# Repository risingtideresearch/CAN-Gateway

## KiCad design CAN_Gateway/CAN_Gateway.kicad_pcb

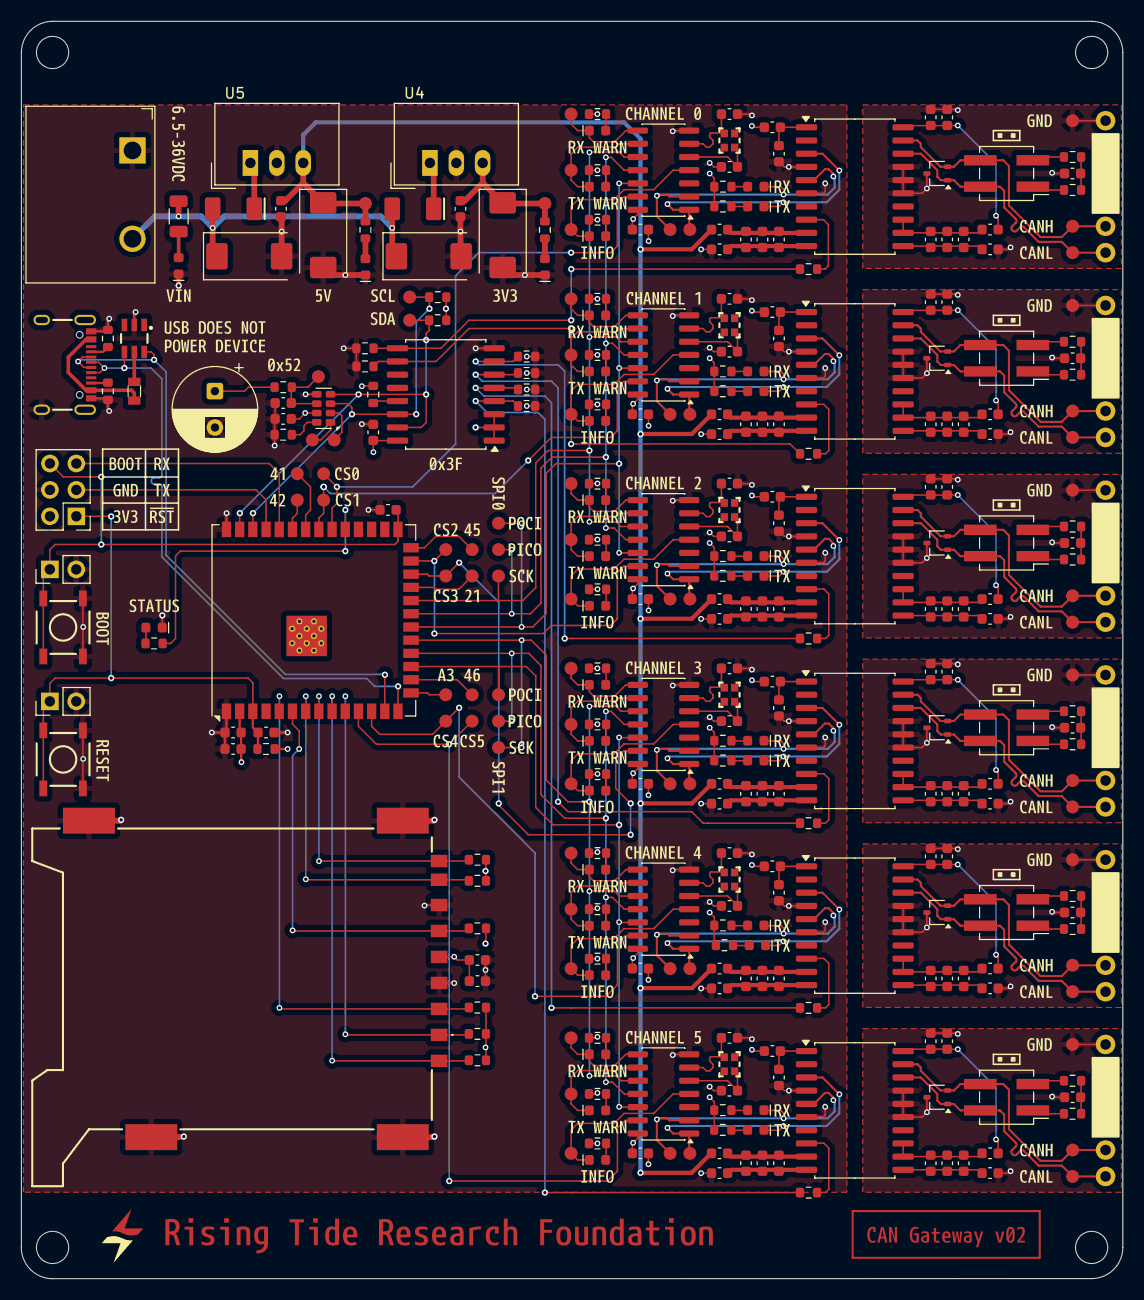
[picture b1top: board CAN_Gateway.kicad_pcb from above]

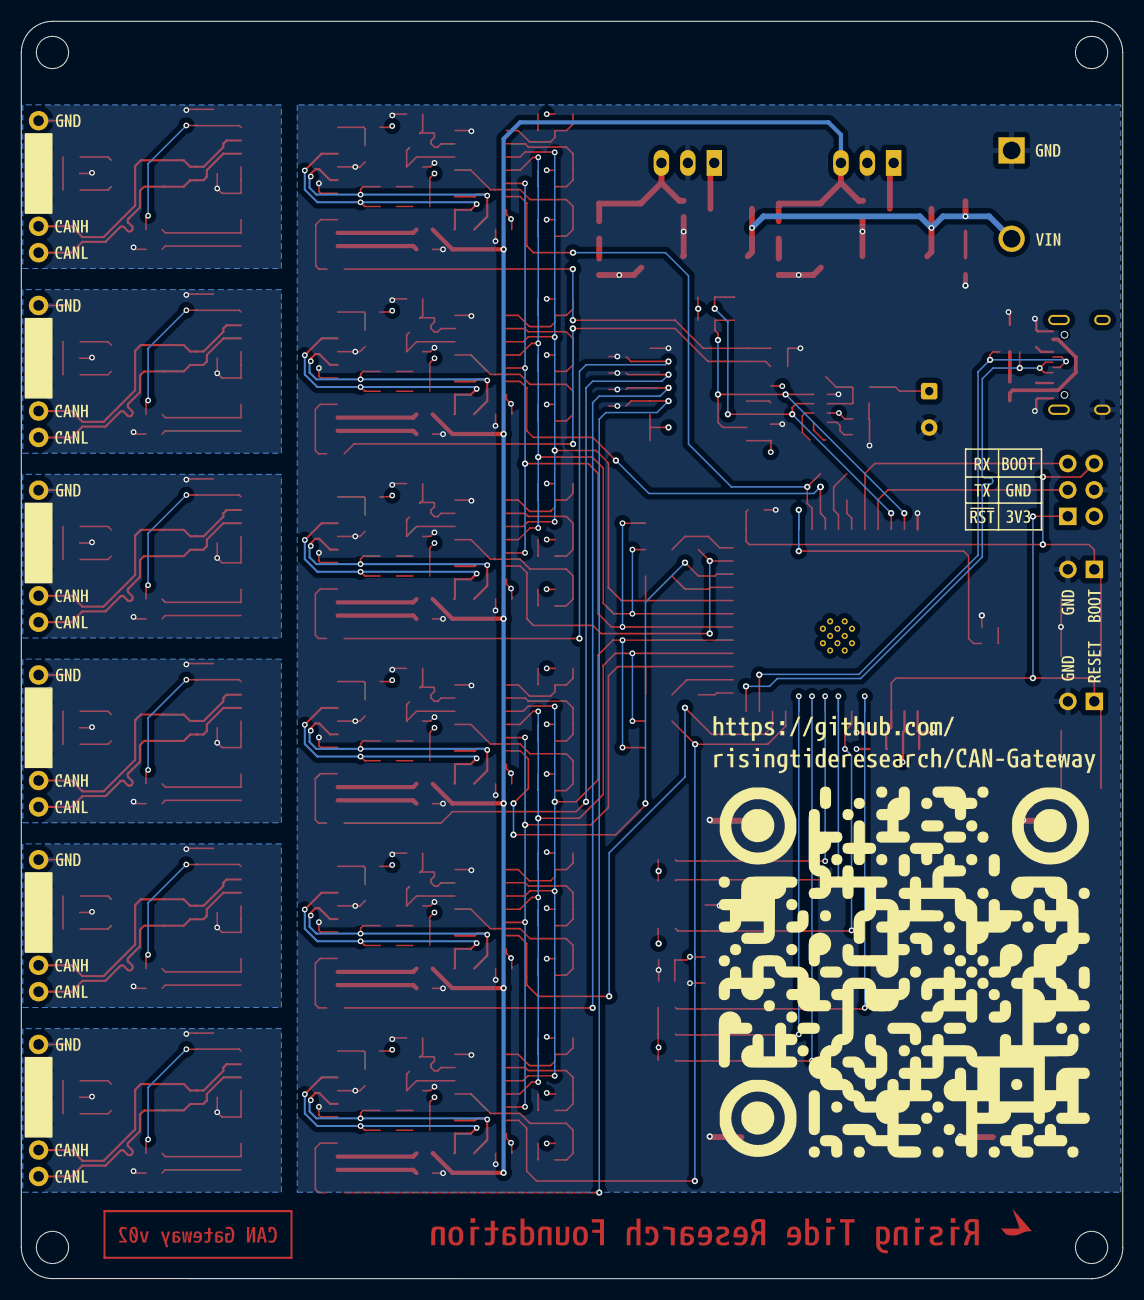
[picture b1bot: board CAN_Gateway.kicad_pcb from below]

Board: 4 copper layers, 106.0 x 121.0 mm, 481 parts (31 on the bottom side), 209 nets.

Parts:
C1, C3, C7, C16, C20, C21, C23, C27, C30, C37, C39, C43, C52, C54, C56, C60, C67, C69, C73, C83, C85, C89, C90: 0.1uF; C_0603_1608Metric
C2, C6, C12, C17, C22, C26, C33, C38, C42, C46, C55, C59, C63, C68, C72, C77, C81, C84, C88, C93: 10uF; C_0603_1608Metric
C4, C14, C24, C35, C40, C48, C50, C51, C57, C65, C70, C79, C86, C95: 10nF; C_0603_1608Metric
C5, C13, C25, C34, C41, C47, C58, C64, C71, C74, C78, C87, C94: 1.0uF; C_0603_1608Metric
C10, C31, C44, C61, C75, C91: 4.7nF; C_0603_1608Metric
C11, C15, C32, C36, C45, C49, C62, C66, C76, C80, C92, C96: 15pF; C_0603_1608Metric
C18, C19, C28, C29: 10uF; CP_EIA-7343-30_AVX-N
C53: 1F; CP_Radial_D8.0mm_P3.50mm
C82: 4.7uF; C_0603_1608Metric
D1, D2, D3, D10, D11, D12, D17, D18, D19, D23, D24, D25, D29, D30, D31, D36, D37, D38, D42, D43, D44: Red; LED_0603_1608Metric
D4, D5, D13, D14, D20, D21, D26, D27, D32, D33, D39, D40: Green; LED_0603_1608Metric
D7, D16, D22, D28, D34, D41: ESD2CANxx24-Q1; SOT-323_SC-70
D8, D15: SK34A; SMA
D9: DT1042-04SO; SOT23-6
D35: Blue; LED_0603_1608Metric
F1: 6V/0.5A/1A; 0805
J1, J6, J8, J10, J12, J19: Conn 01x06 Socket; 1x06
J2: Screw Terminal 2Pos 8.5mm Pitch; TerminalBlock_DoraboDBT10_8.5mm
J3, J7, J9, J11, J15, J18: Conn_02x02_Pin; PinHeader_2x02_P2.54mm_Vertical_SMD
J4: USB-C Receptacle; USB-C_16
J5: SDCard Push-Lock FPS009-4200-0; SDCard_PushLock_FPS00942000
J13: Conn 02x03 Odd Even; PinHeader_2x03_P2.54mm_Vertical
J14, J17: Conn 01x02 Pin; PinHeader_1x02_P2.54mm_Vertical
L1, L2, L3, L4, L5, L6, L7, L8, L9, L10, L11, L12, L13, L14, L15, L16, L17, L18, L19, L20, L21, L22, L23, L24, L25, L26, L27, L28, L29, L30: 330 OHM; C_0603_1608Metric
R1, R2, R3, R16, R17, R18, R23, R24, R25, R33, R34, R35, R40, R41, R42, R51, R52, R53: 330; R_0603_1608Metric
R4, R5, R19, R20, R26, R27, R36, R37, R43, R44, R54, R55: 68; R_0603_1608Metric
R6, R7, R21, R22, R28, R29, R38, R39, R48, R49, R59, R60: 60.4R; R_0603_1608Metric
R8, R9, R10, R11, R12, R13, R31, R32, R45, R61, R62, R63, R64, R65, R66: 10k; R_0603_1608Metric
R14, R15: 5.1k; R_0603_1608Metric
R30, R57: 1k; R_0603_1608Metric
R46, R47: 2.2k; R_0603_1608Metric
R50, R58: 470; R_0603_1608Metric
R56: 2.0k; R_1206_3216Metric
R67, R68, R69, R70, R71, R72: 4.7k; R_0603_1608Metric
SW1, SW2: SMD_5.2x5.2mm_h1.9mm; Push_SMD_5.2x5.2mm_h1.9mm
TP1, TP2, TP3, TP4, TP5, TP6, TP7, TP8, TP9, TP10, TP11, TP12, TP13, TP14, TP15, TP16, TP17, TP18, TP19, TP20, TP21, TP22, TP23, TP24, TP25, TP26, TP27, TP28, TP29, TP30, TP31, TP32, TP33, TP34, TP35, TP36, TP37, TP38, TP39, TP40, TP41, TP42, TP43, TP44, TP45, TP46, TP47, TP48, TP49, TP50, TP51, TP52, TP53, TP54, TP55, TP56, TP57, TP58, TP59, TP60, TP61, TP62, TP63, TP64, TP65, TP66, TP67, TP68, TP69, TP70, TP71, TP72, TP73: 1.25mm; TestPoint-1.25mm
U2, U6, U8, U12, U14, U17: ISOW1044; SOIC-20W_7.5x12.8mm_P1.27mm
U3, U7, U9, U13, U15, U18: MCP2518FD; SOIC-14_3.9x8.7mm_P1.27mm
U4: DCDC TSR1-2433E 3.3V; Converter_DCDC_TRACO_TSR-1_THT
U5: DCDC TSR1-2450E 5V; Converter_DCDC_TRACO_TSR-1_THT
U10: RV-3028-C7; MicroCrystal_C7_SON-8_1.5x3.2mm_P0.9mm
U11: TCA9534; SOIC-16W_7.5x10.3mm_P1.27mm
U16: ESP32-S3-WROOM-1U-N16R2; ESP32-S3-WROOM-1U
Y1, Y2, Y3, Y4, Y5, Y6: 20MHz; Crystal_SMD_2.0x1.6mm
kibuzzard-69A580A1: G***; kibuzzard-69A580A1
kibuzzard-69A580AE: G***; kibuzzard-69A580AE
kibuzzard-69A580BE: G***; kibuzzard-69A580BE
kibuzzard-69A580C7: G***; kibuzzard-69A580C7
kibuzzard-69A580D6: G***; kibuzzard-69A580D6
kibuzzard-69A580DE: G***; kibuzzard-69A580DE
kibuzzard-69A58259: G***; kibuzzard-69A58259
kibuzzard-699FC53E: G***; kibuzzard-699FC53E
kibuzzard-699FC70E, kibuzzard-699FC70E#2, kibuzzard-699FC70E#3, kibuzzard-699FC70E#4, kibuzzard-699FC70E#5, kibuzzard-699FC70E#6, kibuzzard-699FC70E#7, kibuzzard-699FC70E#8, kibuzzard-699FC70E#9, kibuzzard-699FC70E#10, kibuzzard-699FC70E#11, kibuzzard-699FC70E#12: G***; kibuzzard-699FC70E
kibuzzard-699FC89D, kibuzzard-699FC89D#2, kibuzzard-699FC89D#3, kibuzzard-699FC89D#4, kibuzzard-699FC89D#5, kibuzzard-699FC89D#6: G***; kibuzzard-699FC89D
kibuzzard-699FC682: G***; kibuzzard-699FC682
kibuzzard-699FC727, kibuzzard-699FC727#2, kibuzzard-699FC727#3, kibuzzard-699FC727#4, kibuzzard-699FC727#5, kibuzzard-699FC727#6, kibuzzard-699FC727#7, kibuzzard-699FC727#8, kibuzzard-699FC727#9, kibuzzard-699FC727#10, kibuzzard-699FC727#11, kibuzzard-699FC727#12: G***; kibuzzard-699FC727
kibuzzard-699FC895, kibuzzard-699FC895#2, kibuzzard-699FC895#3, kibuzzard-699FC895#4, kibuzzard-699FC895#5, kibuzzard-699FC895#6: G***; kibuzzard-699FC895
kibuzzard-699FCC6A, kibuzzard-699FCC6A#2, kibuzzard-699FCC6A#3, kibuzzard-699FCC6A#4, kibuzzard-699FCC6A#5, kibuzzard-699FCC6A#6: G***; kibuzzard-699FCC6A
kibuzzard-699FCC73, kibuzzard-699FCC73#2, kibuzzard-699FCC73#3, kibuzzard-699FCC73#4, kibuzzard-699FCC73#5, kibuzzard-699FCC73#6: G***; kibuzzard-699FCC73
kibuzzard-699FCC79, kibuzzard-699FCC79#2, kibuzzard-699FCC79#3, kibuzzard-699FCC79#4, kibuzzard-699FCC79#5, kibuzzard-699FCC79#6: G***; kibuzzard-699FCC79
kibuzzard-699FD0A7: G***; kibuzzard-699FD0A7
kibuzzard-699FD0AC: G***; kibuzzard-699FD0AC
kibuzzard-699FD0B2: G***; kibuzzard-699FD0B2
kibuzzard-699FD0B9: G***; kibuzzard-699FD0B9
kibuzzard-699FD0BF: G***; kibuzzard-699FD0BF
kibuzzard-699FD1A2: G***; kibuzzard-699FD1A2
kibuzzard-699FD1B1, kibuzzard-699FD1B1#2: G***; kibuzzard-699FD1B1
kibuzzard-699FD1CD: G***; kibuzzard-699FD1CD
kibuzzard-699FD1DB: G***; kibuzzard-699FD1DB
kibuzzard-699FD2FA, kibuzzard-699FD2FA#2: G***; kibuzzard-699FD2FA
kibuzzard-699FD3EC: G***; kibuzzard-699FD3EC
kibuzzard-699FD05A: G***; kibuzzard-699FD05A
kibuzzard-699FD6AC: G***; kibuzzard-699FD6AC
kibuzzard-699FD6B7: G***; kibuzzard-699FD6B7
kibuzzard-699FD7B6: G***; kibuzzard-699FD7B6
kibuzzard-699FD010, kibuzzard-699FD010#2, kibuzzard-699FD010#3, kibuzzard-699FD010#4, kibuzzard-699FD010#5, kibuzzard-699FD010#6, kibuzzard-699FD010#7, kibuzzard-699FD010#8, kibuzzard-699FD010#9, kibuzzard-699FD010#10, kibuzzard-699FD010#11, kibuzzard-699FD010#12: G***; kibuzzard-699FD010
kibuzzard-699FD27D, kibuzzard-699FD27D#2: G***; kibuzzard-699FD27D
kibuzzard-699FD28D, kibuzzard-699FD28D#2: G***; kibuzzard-699FD28D
kibuzzard-699FD31B, kibuzzard-699FD31B#2: G***; kibuzzard-699FD31B
kibuzzard-699FD36B: G***; kibuzzard-699FD36B
kibuzzard-699FD67D: G***; kibuzzard-699FD67D
kibuzzard-699FD77B: G***; kibuzzard-699FD77B
kibuzzard-699FD269, kibuzzard-699FD269#2: G***; kibuzzard-699FD269
kibuzzard-699FD306, kibuzzard-699FD306#2, kibuzzard-699FD306#3, kibuzzard-699FD306#4, kibuzzard-699FD306#5: G***; kibuzzard-699FD306
kibuzzard-699FD386, kibuzzard-699FD386#2: G***; kibuzzard-699FD386
kibuzzard-699FD396: G***; kibuzzard-699FD396
kibuzzard-699FD567: G***; kibuzzard-699FD567
kibuzzard-699FD585: G***; kibuzzard-699FD585
kibuzzard-699FD699: G***; kibuzzard-699FD699
kibuzzard-699FD750: G***; kibuzzard-699FD750
kibuzzard-699FDA3C, kibuzzard-699FDA3C#2: G***; kibuzzard-699FDA3C
kibuzzard-699FDA5E, kibuzzard-699FDA5E#2: G***; kibuzzard-699FDA5E
kibuzzard-699FDA54, kibuzzard-699FDA54#2: G***; kibuzzard-699FDA54
kibuzzard-699FDA91: G***; kibuzzard-699FDA91
kibuzzard-699FDAA6: G***; kibuzzard-699FDAA6
kibuzzard-699FE3A4: G***; kibuzzard-699FE3A4
kibuzzard-699FE10E: G***; kibuzzard-699FE10E

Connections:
3.3V: C7.1, C16.1, C17.1, C19.1, C20.1, C27.1, C43.1, C51.1, C52.1, C60.1, C73.1, C81.1, C82.1, C89.1, J5.4 (VDD), J13.2, L1.1, L6.1, L11.1, L16.1, L21.1, L26.1, R1.2, R2.2, R3.2, R4.2, R5.2, R8.2, R9.2, R10.2, R11.2, R12.2, R13.2, R16.2, R17.2, R18.2, R19.2, R20.2, R23.2, R24.2, R25.2, R26.2, R27.2, R31.2, R33.2, R34.2, R35.2, R36.2, R37.2, R40.2, R41.2, R42.2, R43.2, R44.2, R45.2, R46.2, R47.1, R51.2, R52.2, R53.2, R54.2, R55.2, R58.2, TP9.1, U3.14 (VDD), U4.3 (Vout), U7.14 (VDD), U9.14 (VDD), U10.7 (VDD), U11.1 (A0), U11.2 (A1), U11.3 (A2), U11.16 (VDD), U13.14 (VDD), U15.14 (VDD), U16.2 (VDD), U18.14 (VDD)
5V: C29.1, C30.1, L4.1, L9.1, L14.1, L19.1, L24.1, L29.1, R57.2, TP12.1, U5.3 (Vout)
/CAN0+: D4.1 (K), TP2.1, U2.5 (RXD), U3.2 (RXCAN)
/CAN0-: D5.1 (K), TP3.1, U2.3 (TXD), U3.1 (TXCAN)
/CAN0_N: D7.1 (A1), J3.2, J19.6, TP5.1, U2.18 (CANL)
/CAN0_P: D7.2 (A2), J3.4, J19.5, TP4.1, U2.19 (CANH)
/CAN1+: D13.1 (K), TP11.1, U6.5 (RXD), U7.2 (RXCAN)
/CAN1-: D14.1 (K), TP13.1, U6.3 (TXD), U7.1 (TXCAN)
/CAN1_N: D16.1 (A1), J1.6, J7.2, TP15.1, U6.18 (CANL)
/CAN1_P: D16.2 (A2), J1.5, J7.4, TP14.1, U6.19 (CANH)
/CAN2+: D20.1 (K), TP20.1, U8.5 (RXD), U9.2 (RXCAN)
/CAN2-: D21.1 (K), TP21.1, U8.3 (TXD), U9.1 (TXCAN)
/CAN2_N: D22.1 (A1), J6.6, J9.2, TP23.1, U8.18 (CANL)
/CAN2_P: D22.2 (A2), J6.5, J9.4, TP22.1, U8.19 (CANH)
/CAN3+: D26.1 (K), TP31.1, U12.5 (RXD), U13.2 (RXCAN)
/CAN3-: D27.1 (K), TP32.1, U12.3 (TXD), U13.1 (TXCAN)
/CAN3_N: D28.1 (A1), J8.6, J11.2, TP34.1, U12.18 (CANL)
/CAN3_P: D28.2 (A2), J8.5, J11.4, TP33.1, U12.19 (CANH)
/CAN4+: D32.1 (K), TP39.1, U14.5 (RXD), U15.2 (RXCAN)
/CAN4-: D33.1 (K), TP42.1, U14.3 (TXD), U15.1 (TXCAN)
/CAN4_N: D34.1 (A1), J10.6, J15.2, TP44.1, U14.18 (CANL)
/CAN4_P: D34.2 (A2), J10.5, J15.4, TP43.1, U14.19 (CANH)
/CAN5+: D39.1 (K), TP49.1, U17.5 (RXD), U18.2 (RXCAN)
/CAN5-: D40.1 (K), TP50.1, U17.3 (TXD), U18.1 (TXCAN)
/CAN5_N: D41.1 (A1), J12.6, J18.2, TP52.1, U17.18 (CANL)
/CAN5_P: D41.2 (A2), J12.5, J18.4, TP51.1, U17.19 (CANH)
CAN0_EN: R65.2, R67.1, U11.9 (P4)
CAN1_EN: R66.2, R68.1, U11.10 (P5)
CAN2_EN: R64.2, R69.1, U11.7 (P3)
CAN3_EN: R63.2, R70.1, U11.6 (P2)
CAN4_EN: R62.2, R71.1, U11.5 (P1)
CAN5_EN: R61.2, R72.1, U11.4 (P0)
CS_CAN0: TP60.1, U3.13 (~CS), U16.32 (IO39)
CS_CAN1: TP61.1, U7.13 (~CS), U16.33 (IO40)
CS_CAN2: TP65.1, U9.13 (~CS), U16.25 (IO48)
CS_CAN3: TP64.1, U13.13 (~CS), U16.24 (IO47)
CS_CAN4: TP58.1, U15.13 (~CS), U16.12 (IOA8)
CS_CAN5: TP59.1, U16.11 (IOA18), U18.13 (~CS)
ESP32_EN: C74.1, J13.1, J14.1, R45.1, SW1.2, U16.3 (EN)
ESP32_RXD: J13.5, U16.36 (RXD0/IO44)
ESP32_TXD: J13.3, U16.37 (TXD0/IO43)
ESP_BOOT: C90.1, J13.6, J17.1, SW2.2, U16.27 (IO0)
ESP_STATUS: R50.2, U16.31 (IO38)
GND: C3.1, C7.2, C11.1, C15.1, C16.2, C17.2, C18.2, C19.2, C20.2, C23.1, C27.2, C28.2, C29.2, C30.2, C32.1, C36.1, C39.1, C43.2, C45.1, C49.1, C50.2, C51.2, C52.2, C53.2, C56.1, C60.2, C62.1, C66.1, C69.1, C73.2, C74.2, C76.1, C80.1, C81.2, C82.2, C85.1, C89.2, C90.2, C92.1, C96.1, D9.2 (GND), D35.1 (K), D42.1 (K), D43.1 (K), D44.1 (K), J2.1, J4.GND, J4.S (SHIELD), J5.3 (VSS), J5.6 (VSS), J5.10 (SHIELD), J5.11 (SHIELD), J5.12 (SHIELD), J5.13 (SHIELD), J13.4, J14.2, J17.2, L5.1, L10.1, L15.1, L20.1, L25.1, L30.1, R14.1, R15.1, R32.1, R61.1, R62.1, R63.1, R64.1, R65.1, R66.1, SW1.1, SW2.1, U2.4 (STB), U2.6 (GNDIO), U3.7 (VSS), U4.2 (GND), U5.2 (GND), U6.4 (STB), U6.6 (GNDIO), U7.7 (VSS), U8.4 (STB), U8.6 (GNDIO), U9.7 (VSS), U10.5 (VSS), U11.8 (GND), U12.4 (STB), U12.6 (GNDIO), U13.7 (VSS), U14.4 (STB), U14.6 (GNDIO), U15.7 (VSS), U16.1 (GND), U16.40 (GND), U17.4 (STB), U17.6 (GNDIO), U18.7 (VSS)
ISOGND0: C1.1, C2.1, C10.2, D7.3 (common), J19.1, L3.2, TP1.1, U2.15 (GISOIN), U2.16 (GISOIN), U2.17 (GISOIN)
ISOGND1: C21.1, C22.1, C31.2, D16.3 (common), J1.1, L8.2, TP10.1, U6.15 (GISOIN), U6.16 (GISOIN), U6.17 (GISOIN)
ISOGND2: C37.1, C38.1, C44.2, D22.3 (common), J6.1, L13.2, TP19.1, U8.15 (GISOIN), U8.16 (GISOIN), U8.17 (GISOIN)
ISOGND3: C54.1, C55.1, C61.2, D28.3 (common), J8.1, L18.2, TP30.1, U12.15 (GISOIN), U12.16 (GISOIN), U12.17 (GISOIN)
ISOGND4: C67.1, C68.1, C75.2, D34.3 (common), J10.1, L23.2, TP38.1, U14.15 (GISOIN), U14.16 (GISOIN), U14.17 (GISOIN)
ISOGND5: C83.1, C84.1, C91.2, D41.3 (common), J12.1, L28.2, TP48.1, U17.15 (GISOIN), U17.16 (GISOIN), U17.17 (GISOIN)
unnamed: C10.1, R6.2, R7.1
unnamed: C31.1, R21.2, R22.1
unnamed: C44.1, R28.2, R29.1
unnamed: C53.1, R30.1
unnamed: C61.1, R38.2, R39.1
unnamed: C75.1, R48.2, R49.1
unnamed: C91.1, R59.2, R60.1
unnamed: D1.2 (A), R1.1
unnamed: D1.1 (K), TP6.1, U3.4 (~INT)
unnamed: D2.2 (A), R2.1
unnamed: D2.1 (K), TP7.1, U3.9 (~INT0)
unnamed: D3.2 (A), R3.1
unnamed: D3.1 (K), TP8.1, U3.8 (~INT1)
unnamed: D4.2 (A), R4.1
unnamed: D5.2 (A), R5.1
unnamed: D8.C (K), U4.1 (Vin)
unnamed: D10.2 (A), R16.1
unnamed: D10.1 (K), TP16.1, U7.4 (~INT)
unnamed: D11.2 (A), R17.1
unnamed: D11.1 (K), TP17.1, U7.9 (~INT0)
unnamed: D12.2 (A), R18.1
unnamed: D12.1 (K), TP18.1, U7.8 (~INT1)
unnamed: D13.2 (A), R19.1
unnamed: D14.2 (A), R20.1
unnamed: D15.C (K), U5.1 (Vin)
unnamed: D17.2 (A), R23.1
unnamed: D17.1 (K), TP25.1, U9.4 (~INT)
unnamed: D18.2 (A), R24.1
unnamed: D18.1 (K), TP26.1, U9.9 (~INT0)
unnamed: D19.2 (A), R25.1
unnamed: D19.1 (K), TP27.1, U9.8 (~INT1)
unnamed: D20.2 (A), R26.1
unnamed: D21.2 (A), R27.1
unnamed: D23.2 (A), R33.1
unnamed: D23.1 (K), TP35.1, U13.4 (~INT)
unnamed: D24.2 (A), R34.1
unnamed: D24.1 (K), TP36.1, U13.9 (~INT0)
unnamed: D25.2 (A), R35.1
unnamed: D25.1 (K), TP37.1, U13.8 (~INT1)
unnamed: D26.2 (A), R36.1
unnamed: D27.2 (A), R37.1
unnamed: D29.2 (A), R40.1
unnamed: D29.1 (K), TP45.1, U15.4 (~INT)
unnamed: D30.2 (A), R41.1
unnamed: D30.1 (K), TP46.1, U15.9 (~INT0)
unnamed: D31.2 (A), R42.1
unnamed: D31.1 (K), TP47.1, U15.8 (~INT1)
unnamed: D32.2 (A), R43.1
unnamed: D33.2 (A), R44.1
unnamed: D35.2 (A), R50.1
unnamed: D36.2 (A), R51.1
unnamed: D36.1 (K), TP53.1, U18.4 (~INT)
unnamed: D37.2 (A), R52.1
unnamed: D37.1 (K), TP54.1, U18.9 (~INT0)
unnamed: D38.2 (A), R53.1
unnamed: D38.1 (K), TP55.1, U18.8 (~INT1)
unnamed: D39.2 (A), R54.1
unnamed: D40.2 (A), R55.1
unnamed: D42.2 (A), R56.1
unnamed: D43.2 (A), R57.1
unnamed: D44.2 (A), R58.1
unnamed: F1.1, J4.VBUS
unnamed: J3.1, R7.2
unnamed: J3.3, R6.1
unnamed: J4.A5 (CC1), R15.2
unnamed: J4.B5 (CC2), R14.2
unnamed: J7.1, R22.2
unnamed: J7.3, R21.1
unnamed: J9.1, R29.2
unnamed: J9.3, R28.1
unnamed: J11.1, R39.2
unnamed: J11.3, R38.1
unnamed: J15.1, R49.2
unnamed: J15.3, R48.1
unnamed: J18.1, R60.2
unnamed: J18.3, R59.1
unnamed: R67.2, U2.8 (EN/FLT)
unnamed: C12.2, C13.2, C14.2, L5.2, U2.10 (GND1)
unnamed: C4.2, C5.2, C6.2, L3.1, U2.11 (GND2)
unnamed: C12.1, C13.1, C14.1, L4.2, U2.9 (VDD)
unnamed: C3.2, L1.2, U2.1 (VIO)
unnamed: C1.2, C2.2, L2.2, U2.20 (VISOIN)
unnamed: C4.1, C5.1, C6.1, L2.1, U2.12 (VISOOUT), U2.13 (VSIN)
unnamed: C15.2, U3.6 (OSC1), Y1.1
unnamed: C11.2, U3.5 (OSC2), Y1.2
unnamed: R68.2, U6.8 (EN/FLT)
unnamed: C33.2, C34.2, C35.2, L10.2, U6.10 (GND1)
unnamed: C24.2, C25.2, C26.2, L8.1, U6.11 (GND2)
unnamed: C33.1, C34.1, C35.1, L9.2, U6.9 (VDD)
unnamed: C23.2, L6.2, U6.1 (VIO)
unnamed: C21.2, C22.2, L7.2, U6.20 (VISOIN)
unnamed: C24.1, C25.1, C26.1, L7.1, U6.12 (VISOOUT), U6.13 (VSIN)
unnamed: C36.2, U7.6 (OSC1), Y2.1
unnamed: C32.2, U7.5 (OSC2), Y2.2
unnamed: R69.2, U8.8 (EN/FLT)
unnamed: C46.2, C47.2, C48.2, L15.2, U8.10 (GND1)
unnamed: C40.2, C41.2, C42.2, L13.1, U8.11 (GND2)
unnamed: C46.1, C47.1, C48.1, L14.2, U8.9 (VDD)
unnamed: C39.2, L11.2, U8.1 (VIO)
unnamed: C37.2, C38.2, L12.2, U8.20 (VISOIN)
unnamed: C40.1, C41.1, C42.1, L12.1, U8.12 (VISOOUT), U8.13 (VSIN)
unnamed: C49.2, U9.6 (OSC1), Y3.1
unnamed: C45.2, U9.5 (OSC2), Y3.2
unnamed: TP29.1, U10.1 (CLKOUT)
unnamed: R32.2, U10.8 (EVI)
unnamed: TP28.1, U10.2 (~INT)
unnamed: R31.1, U11.13 (~INT)
unnamed: R70.2, U12.8 (EN/FLT)
unnamed: C63.2, C64.2, C65.2, L20.2, U12.10 (GND1)
unnamed: C57.2, C58.2, C59.2, L18.1, U12.11 (GND2)
unnamed: C63.1, C64.1, C65.1, L19.2, U12.9 (VDD)
unnamed: C56.2, L16.2, U12.1 (VIO)
unnamed: C54.2, C55.2, L17.2, U12.20 (VISOIN)
unnamed: C57.1, C58.1, C59.1, L17.1, U12.12 (VISOOUT), U12.13 (VSIN)
unnamed: C66.2, U13.6 (OSC1), Y4.1
unnamed: C62.2, U13.5 (OSC2), Y4.2
unnamed: R71.2, U14.8 (EN/FLT)
unnamed: C77.2, C78.2, C79.2, L25.2, U14.10 (GND1)
unnamed: C70.2, C71.2, C72.2, L23.1, U14.11 (GND2)
unnamed: C77.1, C78.1, C79.1, L24.2, U14.9 (VDD)
unnamed: C69.2, L21.2, U14.1 (VIO)
unnamed: C67.2, C68.2, L22.2, U14.20 (VISOIN)
unnamed: C70.1, C71.1, C72.1, L22.1, U14.12 (VISOOUT), U14.13 (VSIN)
unnamed: C80.2, U15.6 (OSC1), Y5.1
unnamed: C76.2, U15.5 (OSC2), Y5.2
unnamed: TP66.1, U16.23 (IO21)
unnamed: TP62.1, U16.34 (IO41)
unnamed: TP63.1, U16.35 (IO42)
unnamed: TP67.1, U16.26 (IO45)
unnamed: TP57.1, U16.16 (IO46)
unnamed: TP56.1, U16.15 (IOA3)
unnamed: R72.2, U17.8 (EN/FLT)
unnamed: C93.2, C94.2, C95.2, L30.2, U17.10 (GND1)
unnamed: C86.2, C87.2, C88.2, L28.1, U17.11 (GND2)
unnamed: C93.1, C94.1, C95.1, L29.2, U17.9 (VDD)
unnamed: C85.2, L26.2, U17.1 (VIO)
unnamed: C83.2, C84.2, L27.2, U17.20 (VISOIN)
unnamed: C86.1, C87.1, C88.1, L27.1, U17.12 (VISOOUT), U17.13 (VSIN)
unnamed: C96.2, U18.6 (OSC1), Y6.1
unnamed: C92.2, U18.5 (OSC2), Y6.2
RTC_BAT: C50.1, R30.2, TP24.1, U10.6 (VBACKUP)
SCL: R46.1, TP40.1, U10.3 (SCL), U11.14 (SCL), U16.38 (IOA2)
SDA: R47.2, TP41.1, U10.4 (SDA), U11.15 (SDA), U16.39 (IOA1)
SD_CLK: J5.5 (CLK), R9.1, U16.6 (IOA6)
SD_CMD: J5.2 (CMD), R8.1, U16.5 (IOA5)
SD_DAT0: J5.7 (DAT0), R10.1, U16.7 (IOA7)
SD_DAT1: J5.8 (DAT1), R11.1, U16.8 (IOA15)
SD_DAT2: J5.9 (DAT2), R12.1, U16.9 (IOA16)
SD_DAT3: J5.1 (DAT3), R13.1, U16.10 (IOA17)
SPI0_PICO: TP72.1, U3.11 (SI), U7.11 (SI), U9.11 (SI), U16.21 (IOA13)
SPI0_POCI: TP71.1, U3.12 (SO), U7.12 (SO), U9.12 (SO), U16.20 (IOA12)
SPI0_SCK: TP73.1, U3.10 (SCK), U7.10 (SCK), U9.10 (SCK), U16.22 (IOA14)
SPI1_PICO: TP69.1, U13.11 (SI), U15.11 (SI), U16.18 (IOA10), U18.11 (SI)
SPI1_POCI: TP68.1, U13.12 (SO), U15.12 (SO), U16.17 (IOA9), U18.12 (SO)
SPI1_SCK: TP70.1, U13.10 (SCK), U15.10 (SCK), U16.19 (IOA11), U18.10 (SCK)
USB_DN: D9.6 (I/O4), J4.A7 (D-), J4.B7 (D-), U16.13 (IOA19)
USB_DP: D9.4 (I/O3), J4.A6 (D+), J4.B6 (D+), U16.14 (IOA20)
VIN: C18.1, C28.1, D8.A, D15.A, J2.2, R56.2
VUSB: D9.5 (VCC), F1.2

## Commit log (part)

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2026-06-20 Update to MCP2518
    And general housekeeping before GitHub Project update
2026-06-28 Fix multi-byte SPI transfers
2026-06-28 Remove working files
